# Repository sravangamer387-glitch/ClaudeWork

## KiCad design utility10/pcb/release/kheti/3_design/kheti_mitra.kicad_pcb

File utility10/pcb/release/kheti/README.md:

# Kheti-Mitra irrigation controller - main board (rev B)

Kheti-Mitra irrigation controller: 12 V DC input, 5 V regulator, solenoid-valve driver, two capacitive soil sensors, rain sensor.

**Status: engineering release, software-verified only (ERC on the netlist, KiCad DRC, netlist cross-check, SPICE where noted). Not yet built, not reviewed by a second engineer, not certified.**

## Specification
- Board 86 x 60 mm, 2 layers, 1.6 mm FR-4, 1 oz copper, rounded corners R2.5 mm, 4 x M2.5 mounting holes, 2 fiducials.
- Rules used: min track 0.2 mm (power 0.4 mm), min clearance 0.2 mm, via 0.6/0.3 mm, GND pour on both layers, 132 stitching vias.
- Finish: ENIG recommended (HASL lead-free acceptable); green mask, white silk; IPC class 2.
- 37 parts, 22 nets.

## Circuit description
- 12 V jack -> 1 A PTC -> SMBJ15A TVS -> reverse-polarity PMOS -> +12V; AMS1117-5.0 -> +5V (about 0.3 W at 40 mA).
- Valve: AO3400A low-side switch with 100 ohm gate resistor, 100 k pull-down and SS14 flyback diode; soil sensors on ADC0/ADC1 through 1 k + 100 nF; rain digital input with pull-up.

## Power
Idle about 15 mA at 5 V from 12 V (0.2 W); valve 12 V x 0.3 A during watering.

## Verification
| Check | Result |
|---|---|
| Electrical rule check on the netlist (own ERC: unconnected pins, single-pin nets, output conflicts, unpowered supplies, symbol/footprint pin match) | 0 errors, 0 warnings |
| KiCad DRC | 0 errors, 0 warnings; unconnected pads: 0 |
| Schematic netlist equals PCB netlist | yes |
| Router failures | 0 |
| 3D STEP export | yes |
| Independent Gerber parse (gerbonara): layers parsed, outline size equals the design | 9 layers, outline [86.1, 60.1] mm, match |

Enclosure (prototype shell for 3D printing): outer 101.2 x 75.2 x 23.0 mm, collision/opening check: pass

## Bill of materials
| Ref | Value | Footprint | Manufacturer part | LCSC # | LCSC status |
|---|---|---|---|---|---|
| U1 | ATmega328P-AU | TQFP-32_7x7mm_P0.8mm | ATMEGA328P-AU | C14877 | verified |
| C1 | 100n | C_0603_1608Metric | Samsung CL10B104KB8NNNC 0603 100nF X7R 50V | C1591 | verified |
| C2 | 100n | C_0603_1608Metric | Samsung CL10B104KB8NNNC 0603 100nF X7R 50V | C1591 | verified |
| C3 | 100n | C_0603_1608Metric | Samsung CL10B104KB8NNNC 0603 100nF X7R 50V | C1591 | verified |
| R7 | 10k | R_0603_1608Metric | 0603 10k 1% | C25804 | verified |
| J2 | ISP | PinHeader_2x03_P2.54mm_Vertical | HCTL PZ254-2-03-Z-8.5 (ZHOURI C5116479 had only 340 in stock) | C2894964 | verified |
| D1 | Green | LED_0603_1608Metric | Hubei KENTO KT-0603YG yellow-green 570 nm, Vf about 2 V (lights well from 3.3 V with 1 k; the Everlight 19-217 green was out of stock) | C2289 | verified |
| R5 | 1k | R_0603_1608Metric | 0603 1k 1% | C21190 | verified |
| J1 | 12 V DC in | BarrelJack_CUI_PJ-063AH_Horizontal | CUI/Same Sky PJ-063AH | C22434582 | verified |
| F1 | PTC 1A 16V | Fuse_1812_4532Metric | Littelfuse 1812L110/16DR (1.1 A hold, 16 V) | C142746 | verified |
| D3 | SMBJ15A | D_SMB | Littelfuse SMBJ15A | C83846 | verified |
| Q3 | AO3401A | SOT-23 | AO3401A | C15127 | verified |
| R17 | 100k | R_0603_1608Metric | 0603 100k 1% | C25803 | verified |
| U3 | AMS1117-5.0 | SOT-223-3_TabPin2 | AMS AMS1117-5.0 SOT-223 | C6187 | verified |
| C6 | 10u | C_0805_2012Metric | 0805 10uF X5R | C15850 | verified |
| C7 | 10u | C_0805_2012Metric | 0805 10uF X5R | C15850 | verified |
| C8 | 100n | C_0603_1608Metric | Samsung CL10B104KB8NNNC 0603 100nF X7R 50V | C1591 | verified |
| Q4 | AO3400A | SOT-23 | AOS AO3400A | C20917 | verified |
| R16 | 100 | R_0603_1608Metric | UNI-ROYAL 0603WAF1000T5E | C22775 | verified |
| R18 | 100k | R_0603_1608Metric | 0603 100k 1% | C25803 | verified |
| D7 | SS14 | D_SMA | Starsea SS14 SMA | C84343 | verified |
| J5 | Valve 12V | TerminalBlock_bornier-2_P5.08mm | Cixi Kefa KF128-5.08-2P-AA | C474952 | verified |
| J6 | Soil sensor 1 | JST_PH_B3B-PH-K_1x03_P2.00mm_Vertical | JST B3B-PH-K-S(LF)(SN) | C131339 | verified |
| J7 | Soil sensor 2 | JST_PH_B3B-PH-K_1x03_P2.00mm_Vertical | JST B3B-PH-K-S(LF)(SN) | C131339 | verified |
| J8 | Rain sensor | JST_PH_B3B-PH-K_1x03_P2.00mm_Vertical | JST B3B-PH-K-S(LF)(SN) | C131339 | verified |
| R20 | 1k | R_0603_1608Metric | 0603 1k 1% | C21190 | verified |
| C9 | 100n | C_0603_1608Metric | Samsung CL10B104KB8NNNC 0603 100nF X7R 50V | C1591 | verified |
| R21 | 1k | R_0603_1608Metric | 0603 1k 1% | C21190 | verified |
| C10 | 100n | C_0603_1608Metric | Samsung CL10B104KB8NNNC 0603 100nF X7R 50V | C1591 | verified |
| R22 | 1k | R_0603_1608Metric | 0603 1k 1% | C21190 | verified |
| R23 | 10k | R_0603_1608Metric | 0603 10k 1% | C25804 | verified |
| C11 | 100n | C_0603_1608Metric | Samsung CL10B104KB8NNNC 0603 100nF X7R 50V | C1591 | verified |
| SW2 | Hold | SW_SPST_B3U-1000P | Omron B3U-1000P | C231329 | verified |
| TP1 | TP | TestPoint_Pad_D1.5mm |  |  |  |
| TP2 | TP | TestPoint_Pad_D1.5mm |  |  |  |
| TP3 | TP | TestPoint_Pad_D1.5mm |  |  |  |
| TP4 | TP | TestPoint_Pad_D1.5mm |  |  |  |

`verified` = LCSC number confirmed by web search on 2026-10-31/11-01; `memory` = from my recollection, **check on lcsc.com before ordering**; empty = no number chosen (through-hole connectors, switches, buzzer, test points: hand-assembled or chosen by the buyer). `*_JLC_BOM.csv` / `*_JLC_CPL.csv` list only the parts with an LCSC number; JLCPCB rotation corrections (CPL) must be checked in their viewer.

## Assembly notes
- Reflow (JLCPCB SMT): all SMD parts with an LCSC number. Hand-solder: JST connectors, pin headers, buzzer, switches, test points as listed in the BOM. Fiducials and mounting holes are in the Gerbers.
- Polarity: LED cathode toward GND (silk marks), electrolytic none, diode D2 cathode to +V, Q2 orientation as footprint (SOT-23 pin 1 = gate).
- Programming: ISP header J2 (pin 1 = MISO, square pad). Flash the matching image from `utility10/firmware/release/`: Seeti Counter `4MHz/seeti_prod.hex` (production firmware: timer-triggered 16 kS/s ADC, scan mode to find the real whistle frequency, battery check), Rain Alert `8MHz/rain_alert.hex`, Bijli Meter Reader `8MHz/bijli_meter.hex` (demo-grade firmware, to be hardened).

## Bring-up and test
1. Jack: +12V = 11.9 V, +5V = 5.0 V.
2. Force VALVE_G high from the ISP: the valve switches and the Schottky catches the flyback.
3. Soil sensors: dry about 520 counts / wet about 260 counts (to be calibrated).

## Files
`1_fabrication/` Gerber + drill zip (upload to JLCPCB/any fab), fab notes, copper plot
`2_assembly/` JLC BOM + CPL (SMD parts JLC assembles), full BOM with LCSC numbers for every part, pick-and-place, assembly drawing
`3_design/` KiCad 7 project (pcb, schematic, libs), netlist, STEP model, schematic PDF, renders
`4_enclosure/` printable enclosure (base, screwed lid, battery door, plungers / light pipes / switch extensions) or a mounting plate for a bought IP65 box; dimensions and notes in enclosure.json
`5_verification/` DRC, ERC, verification and readiness reports

## Known limits and review checklist
- Layout was produced by a custom router and software placement; a human layout review (analog routing, ground returns, creepage, connector mechanics, silkscreen) is still required.
- Not verified: EMC, ESD (apart from TVS parts where fitted), thermal, real component tolerances, supplier stock/price, assembly house design-for-manufacture check (run JLCPCB's DFM check on the Gerbers).
- Firmware thresholds are placeholders to be calibrated on prototypes.

## Manufacturing readiness (automatic check)

| Check | Result |
|---|---|
| gerber layers and drill present | PASS |
| drc errors 0 | PASS |
| unconnected 0 | PASS |
| netlist matches schematic | PASS |
| erc errors 0 | PASS |
| independent gerber check clean | PASS |
| every part has lcsc number | PASS |
| every lcsc number verified | PASS |
| cpl rows equal jlc bom parts | PASS |
| step model | PASS |
| KiCad DRC warnings | 0 |
| **Order ready** | **YES** |

Order steps: (1) upload `1_fabrication/*_gerbers.zip`; (2) for assembly upload `2_assembly/*_JLC_BOM.csv` and `*_JLC_CPL.csv`, check the 3D/rotation preview for every polarised part (diodes, ICs, LEDs, electrolytics) because CPL rotations are generated, not hand-checked; (3) buy the through-hole parts listed in `*_BOM_full.csv` marked hand/THT and solder them; (4) re-check stock and the exact LCSC listing for every line before paying.

Limits: the layout is software-generated and has not been reviewed by a PCB engineer; no prototype has been built; the first batch should be treated as a prototype run (order 5 boards).

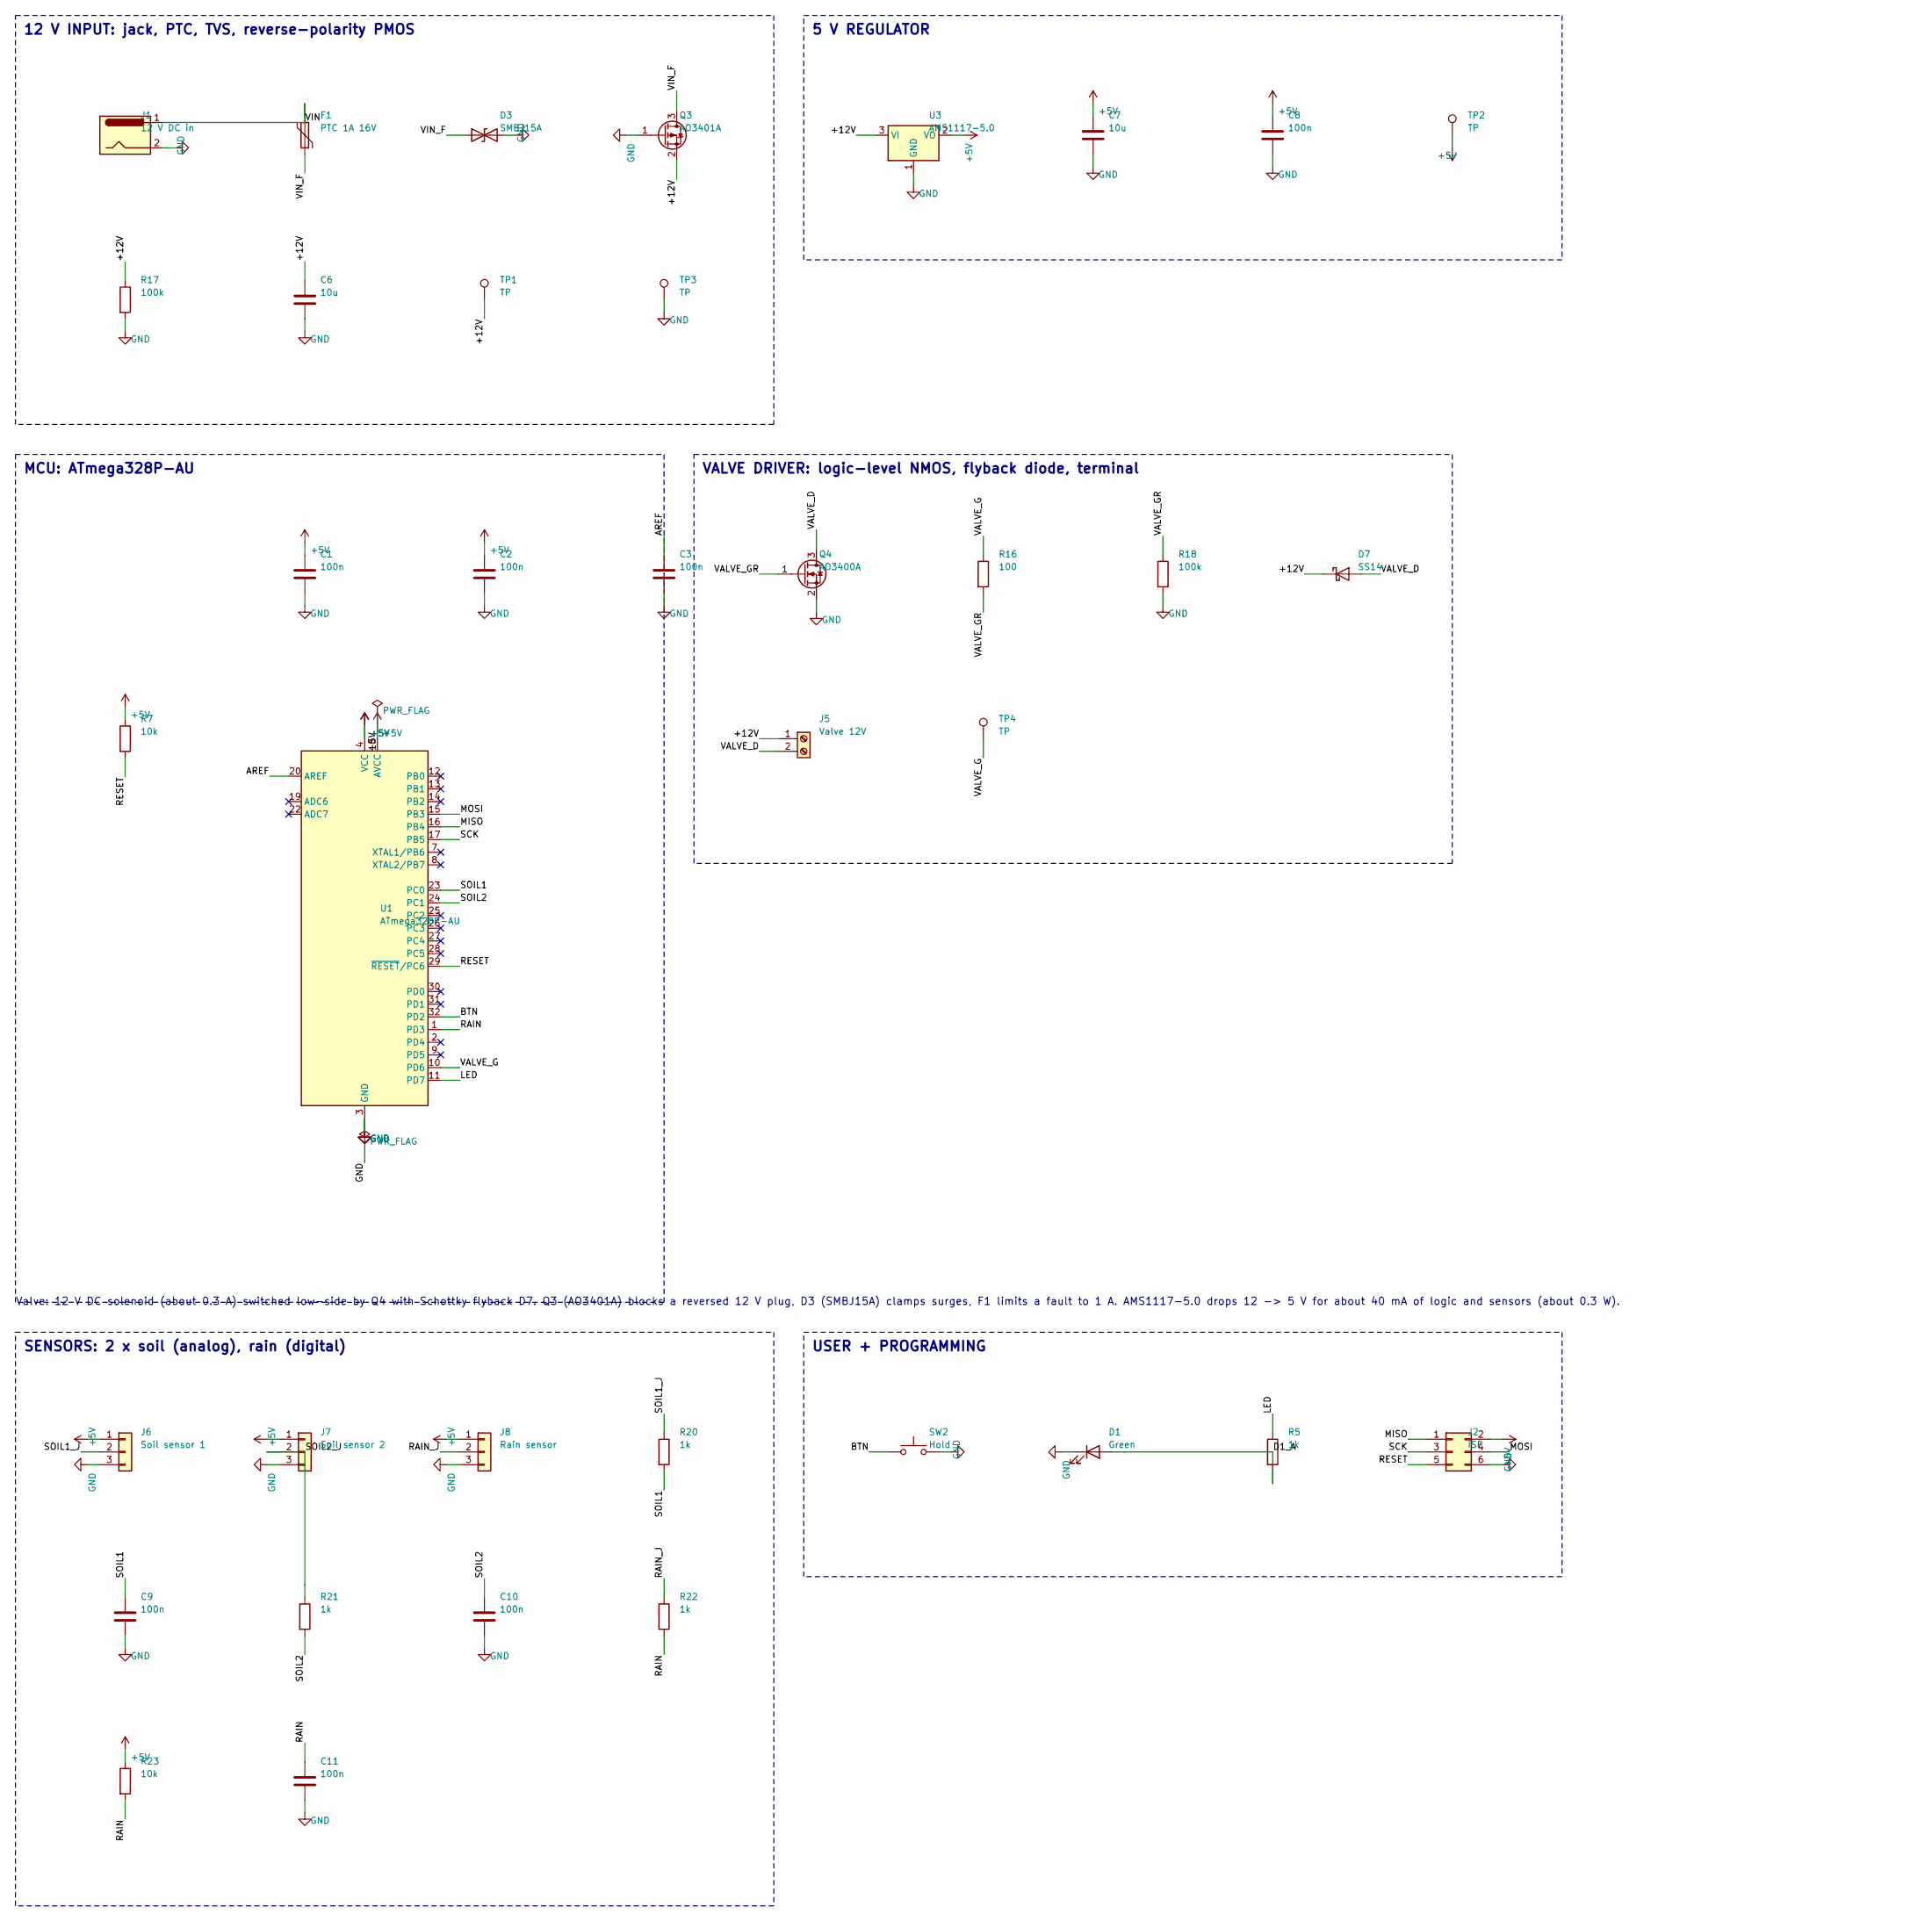
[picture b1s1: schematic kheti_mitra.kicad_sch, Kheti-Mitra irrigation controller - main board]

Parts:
C1, C2, C3, C8, C9, C10, C11: 100n; C_0603_1608Metric
C6, C7: 10u; C_0805_2012Metric
D1: Green; LED_0603_1608Metric
D3: SMBJ15A; D_SMB
D7: SS14; D_SMA
F1: PTC 1A 16V; Fuse_1812_4532Metric
J1: 12 V DC in; BarrelJack_CUI_PJ-063AH_Horizontal
J2: ISP; PinHeader_2x03_P2.54mm_Vertical
J5: Valve 12V; TerminalBlock_bornier-2_P5.08mm
J6: Soil sensor 1; JST_PH_B3B-PH-K_1x03_P2.00mm_Vertical
J7: Soil sensor 2; JST_PH_B3B-PH-K_1x03_P2.00mm_Vertical
J8: Rain sensor; JST_PH_B3B-PH-K_1x03_P2.00mm_Vertical
Q3: AO3401A; SOT-23
Q4: AO3400A; SOT-23
R5, R20, R21, R22: 1k; R_0603_1608Metric
R7, R23: 10k; R_0603_1608Metric
R16: 100; R_0603_1608Metric
R17, R18: 100k; R_0603_1608Metric
SW2: Hold; SW_SPST_B3U-1000P
TP1, TP2, TP3, TP4: TP; TestPoint_Pad_D1.5mm
U1: ATmega328P-AU; TQFP-32_7x7mm_P0.8mm
U3: AMS1117-5.0; SOT-223-3_TabPin2

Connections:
+5V: C1.1, C2.1, C7.1, C8.1, J2.2, J6.1, J7.1, J8.1, R7.1, R23.1, TP2.1, U1.4 (VCC), U1.6 (VCC), U1.18 (AVCC), U3.2 (VO)
+12V: C6.1, D7.1 (K), J5.1, Q3.2 (S), R17.1, TP1.1, U3.3 (VI)
AREF: C3.1, U1.20 (AREF)
BTN: SW2.1, U1.32 (PD2)
D1_A: D1.2 (A), R5.2
GND: C1.2, C2.2, C3.2, C6.2, C7.2, C8.2, C9.2, C10.2, C11.2, D1.1 (K), D3.2 (A2), J1.2, J2.6, J6.3, J7.3, J8.3, Q3.1 (G), Q4.2 (S), R17.2, R18.2, SW2.2, TP3.1, U1.3 (GND), U1.5 (GND), U1.21 (GND), U3.1 (GND)
LED: R5.1, U1.11 (PD7)
MISO: J2.1, U1.16 (PB4)
MOSI: J2.4, U1.15 (PB3)
RAIN: C11.1, R22.2, R23.2, U1.1 (PD3)
RAIN_J: J8.2, R22.1
RESET: J2.5, R7.2, U1.29 (~RESET/PC6)
SCK: J2.3, U1.17 (PB5)
SOIL1: C9.1, R20.2, U1.23 (PC0)
SOIL1_J: J6.2, R20.1
SOIL2: C10.1, R21.2, U1.24 (PC1)
SOIL2_J: J7.2, R21.1
VALVE_D: D7.2 (A), J5.2, Q4.3 (D)
VALVE_G: R16.1, TP4.1, U1.10 (PD6)
VALVE_GR: Q4.1 (G), R16.2, R18.1
VIN: F1.1, J1.1
VIN_F: D3.1 (A1), F1.2, Q3.3 (D)

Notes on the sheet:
12 V INPUT: jack, PTC, TVS, reverse-polarity PMOS
5 V REGULATOR
MCU: ATmega328P-AU
VALVE DRIVER: logic-level NMOS, flyback diode, terminal
SENSORS: 2 x soil (analog), rain (digital)
USER + PROGRAMMING
Valve: 12 V DC solenoid (about 0.3 A) switched low-side by Q4 with Schottky flyback D7. Q3 (AO3401A) blocks a reversed 12 V plug, D3 (SMBJ15A) clamps surges, F1 limits a fault to 1 A. AMS1117-5.0 drops 12 -> 5 V for about 40 mA of logic and sensors (about 0.3 W).

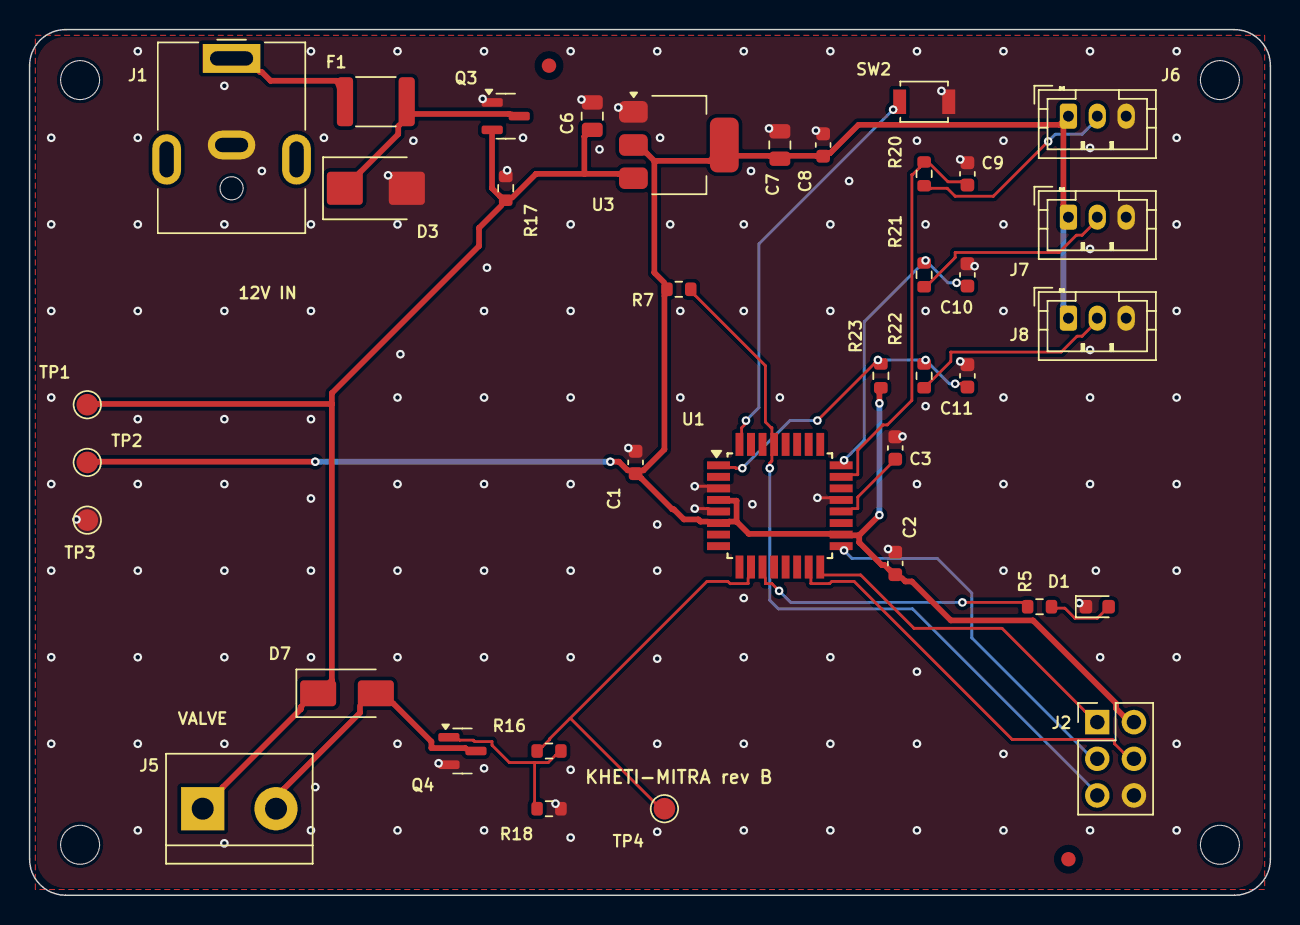
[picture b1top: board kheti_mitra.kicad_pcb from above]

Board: 2 copper layers, 86.0 x 60.0 mm, 43 parts (0 on the bottom side), 22 nets.

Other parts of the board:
FID1, FID2: Fiducial; Fiducial_1mm_Mask2mm
H1, H2, H3, H4: M2.5; MountingHole_2.7mm_M2.5

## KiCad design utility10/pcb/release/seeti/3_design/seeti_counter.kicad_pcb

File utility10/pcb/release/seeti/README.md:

# Seeti Counter - main board (rev B)

Clip-on pressure-cooker whistle counter: electret microphone, band-pass amplifier, ATmega328P-AU, buzzer, LED, 2 x AAA.

**Status: engineering release, software-verified only (ERC on the netlist, KiCad DRC, netlist cross-check, SPICE where noted). Not yet built, not reviewed by a second engineer, not certified.**

## Specification
- Board 64 x 44 mm, 2 layers, 1.6 mm FR-4, 1 oz copper, rounded corners R2.5 mm, 4 x M2.5 mounting holes, 2 fiducials.
- Rules used: min track 0.2 mm (power 0.4 mm), min clearance 0.2 mm, via 0.6/0.3 mm, GND pour on both layers, 54 stitching vias.
- Finish: ENIG recommended (HASL lead-free acceptable); green mask, white silk; IPC class 2.
- 36 parts, 24 nets.

## Circuit description
- **Power:** 2 x AAA (3.0 V fresh, about 2.0 V end of life) -> slide switch SW1 -> AO3401A P-MOSFET Q2 (drain = battery side, source = load, gate = GND) = reverse-battery protection with about 50 mV drop. **Clock:** the ATmega328P is specified for 8 MHz only at 2.7 V and above (1.8 V is allowed up to 4 MHz), and two AAA cells fall below 2.7 V about half-way through their life, so the firmware must switch to 4 MHz at boot (`clock_prescale_set(clock_div_2)`, F_CPU = 4 MHz; ADC clock and the 8 kHz audio sampling still work). Check the speed-grade graph in the current datasheet.
- **Microphone amplifier:** electret capsule biased through R1 2.2 k; AC-coupled (C5 1 uF) into an MCP6001 (rail-to-rail, 1 MHz GBW) non-inverting stage biased at VCC/2 (R2/R3 100 k + C7 10 uF so the feedback return is low impedance). Gain 1 + R8/R9 = 1 + 33k/1k = 34 (SPICE 32.9x at 2.8 kHz); C6 220 nF in the feedback return gives a high-pass at 1/(2 pi R9 C6) = 720 Hz which rejects 100 Hz mains hum and cooking noise before the whistle tone (about 2.8 kHz, to be measured). The amplifier stays flat to about 26 kHz, so **R10 1k + C9 22 nF form a 7.2 kHz first-order anti-alias filter** in front of the ADC; with 16 kS/s sampling this is only a mild filter (about 8 dB at 16 kHz): a known limitation.
- **Digital:** ADC0 reads the amplifier; buzzer through MMBT3904 with flyback diode; button on PD2, LED on PD7; ISP header and a 4-pin UART header (115200 baud debug); reset pulled up by 10 k.

### Simulation: `sim/seeti_amp_results.txt`
```
Closed-loop small-signal response of the Seeti microphone amplifier (Rf = 33k, Rg = 1k, Cg = 220 nF, ideal capsule current source into R1 = 2.2k; MCP6001-class op-amp macro model, GBW 1 MHz) followed by the anti-alias filter R10 1k / C9 22n (-3 dB at 7.2 kHz):
gain at 30 Hz        = 4.4 dB
gain at 1 kHz         = 28.7 dB
gain at 2.8 kHz at amplifier output = 30.4 dB (32.9x); at the ADC pin = 29.7 dB
amplifier -3 dB band  = 700 Hz ... 26.1 kHz (relative to the 30.3 dB passband)
at the ADC pin: 8 kHz = 26.9 dB, 12 kHz = 24.1 dB, 16 kHz = 21.5 dB (relative to 0 dB input)
Production firmware should sample at 16 kS/s (Nyquist 8 kHz): the filter then removes about 8 dB of anything near 16 kHz relative to the 2.8 kHz whistle band. The 8 kS/s demo firmware has little anti-aliasing and relies on the narrow Goertzel bin.
```

### Simulation: `sim/seeti_headroom.txt`
```
Closed-loop gain at 2.8 kHz: 32.8x
VCC 3.0 V: output can swing +/-1.47 V around VMID -> undistorted mic input up to 45 mV peak; a 3 mV peak whistle gives 98 mV peak = 34 ADC counts peak
VCC 2.0 V: output can swing +/-0.97 V around VMID -> undistorted mic input up to 30 mV peak; a 3 mV peak whistle gives 98 mV peak = 50 ADC counts peak
```

## Power
Run current estimate: MCU at 4 MHz and 3 V about 2 mA, amplifier 0.1 mA, microphone bias up to 0.5 mA, LED 1 mA when lit: about 3.6 mA -> 2 x AAA (about 1000 mAh to 2.0 V) gives roughly 250 h of cooking time (estimate, not measured). Add sleep modes in firmware if the unit will stay switched on.

## Verification
| Check | Result |
|---|---|
| Electrical rule check on the netlist (own ERC: unconnected pins, single-pin nets, output conflicts, unpowered supplies, symbol/footprint pin match) | 0 errors, 0 warnings |
| KiCad DRC | 0 errors, 0 warnings; unconnected pads: 0 |
| Schematic netlist equals PCB netlist | yes |
| Router failures | 0 |
| 3D STEP export | yes |
| Independent Gerber parse (gerbonara): layers parsed, outline size equals the design | 9 layers, outline [64.1, 44.1] mm, match |

Enclosure (prototype shell for 3D printing): outer 79.2 x 59.2 x 35.8 mm, collision/opening check: pass

## Bill of materials
| Ref | Value | Footprint | Manufacturer part | LCSC # | LCSC status |
|---|---|---|---|---|---|
| U1 | ATmega328P-AU | TQFP-32_7x7mm_P0.8mm | ATMEGA328P-AU | C14877 | verified |
| U2 | MCP6001 | SOT-23-5 | MCP6001T-I/OT | C116490 | verified |
| J1 | BATT 2xAAA | JST_PH_B2B-PH-K_1x02_P2.00mm_Vertical | JST B2B-PH-K-S(LF)(SN) | C131337 | verified |
| SW1 | Power | SW_SPDT_PCM12 | C&K PCM12SMTR | C221841 | verified |
| Q2 | AO3401A | SOT-23 | AO3401A | C15127 | verified |
| J2 | ISP | PinHeader_2x03_P2.54mm_Vertical | HCTL PZ254-2-03-Z-8.5 (ZHOURI C5116479 had only 340 in stock) | C2894964 | verified |
| J3 | MIC electret | JST_PH_B2B-PH-K_1x02_P2.00mm_Vertical | JST B2B-PH-K-S(LF)(SN) | C131337 | verified |
| J4 | UART | PinHeader_1x04_P2.54mm_Vertical | ZHOURI 2.54-1*4 | C5116483 | verified |
| BZ1 | Buzzer 3V | Buzzer_12x9.5RM7.6 | YUEXIN KC1206 16 ohm passive magnetic 12x9.5 mm (2048 Hz) | C781869 | verified |
| Q1 | MMBT3904 | SOT-23 | MMBT3904 | C20526 | verified |
| D2 | 1N4148WS | D_SOD-323 | 1N4148WS | C2128 | verified |
| SW2 | Target | SW_SPST_B3U-1000P | Omron B3U-1000P | C231329 | verified |
| D1 | Green | LED_0603_1608Metric | Hubei KENTO KT-0603YG yellow-green 570 nm, Vf about 2 V (lights well from 3.3 V with 1 k; the Everlight 19-217 green was out of stock) | C2289 | verified |
| R1 | 2.2k | R_0603_1608Metric | 0603 2.2k 1% | C4190 | verified |
| R2 | 100k | R_0603_1608Metric | 0603 100k 1% | C25803 | verified |
| R3 | 100k | R_0603_1608Metric | 0603 100k 1% | C25803 | verified |
| R4 | 100k | R_0603_1608Metric | 0603 100k 1% | C25803 | verified |
| R5 | 1k | R_0603_1608Metric | 0603 1k 1% | C21190 | verified |
| R6 | 1k | R_0603_1608Metric | 0603 1k 1% | C21190 | verified |
| R7 | 10k | R_0603_1608Metric | 0603 10k 1% | C25804 | verified |
| R8 | 33k | R_0603_1608Metric | UNI-ROYAL 0603WAF3302T5E | C4216 | verified |
| R9 | 1k | R_0603_1608Metric | 0603 1k 1% | C21190 | verified |
| C1 | 100n | C_0603_1608Metric | Samsung CL10B104KB8NNNC 0603 100nF X7R 50V | C1591 | verified |
| C2 | 100n | C_0603_1608Metric | Samsung CL10B104KB8NNNC 0603 100nF X7R 50V | C1591 | verified |
| C3 | 100n | C_0603_1608Metric | Samsung CL10B104KB8NNNC 0603 100nF X7R 50V | C1591 | verified |
| C4 | 10u | C_0805_2012Metric | 0805 10uF X5R | C15850 | verified |
| C5 | 1u | C_0603_1608Metric | 0603 1uF X7R | C15849 | verified |
| C6 | 220n | C_0603_1608Metric | Samsung CL10B224KB8NNNC X7R 50V | C64705 | verified |
| C7 | 10u | C_0805_2012Metric | 0805 10uF X5R | C15850 | verified |
| C8 | 100n | C_0603_1608Metric | Samsung CL10B104KB8NNNC 0603 100nF X7R 50V | C1591 | verified |
| R10 | 1k | R_0603_1608Metric | 0603 1k 1% | C21190 | verified |
| C9 | 22n | C_0603_1608Metric | Samsung CL10B223KB8NNNC X7R | C21122 | verified |
| TP1 | TP | TestPoint_Pad_D1.5mm |  |  |  |
| TP2 | TP | TestPoint_Pad_D1.5mm |  |  |  |
| TP3 | TP | TestPoint_Pad_D1.5mm |  |  |  |
| TP4 | TP | TestPoint_Pad_D1.5mm |  |  |  |

`verified` = LCSC number confirmed by web search on 2026-10-31/11-01; `memory` = from my recollection, **check on lcsc.com before ordering**; empty = no number chosen (through-hole connectors, switches, buzzer, test points: hand-assembled or chosen by the buyer). `*_JLC_BOM.csv` / `*_JLC_CPL.csv` list only the parts with an LCSC number; JLCPCB rotation corrections (CPL) must be checked in their viewer.

## Assembly notes
- Reflow (JLCPCB SMT): all SMD parts with an LCSC number. Hand-solder: JST connectors, pin headers, buzzer, switches, test points as listed in the BOM. Fiducials and mounting holes are in the Gerbers.
- Polarity: LED cathode toward GND (silk marks), electrolytic none, diode D2 cathode to +V, Q2 orientation as footprint (SOT-23 pin 1 = gate).
- Programming: ISP header J2 (pin 1 = MISO, square pad). Flash the matching image from `utility10/firmware/release/`: Seeti Counter `4MHz/seeti_prod.hex` (production firmware: timer-triggered 16 kS/s ADC, scan mode to find the real whistle frequency, battery check), Rain Alert `8MHz/rain_alert.hex`, Bijli Meter Reader `8MHz/bijli_meter.hex` (demo-grade firmware, to be hardened).

## Bring-up and test
1. Insert 2 x AAA with switch OFF; measure BAT_P to GND (J1 pins) = 2.8-3.2 V.
2. Switch ON: TP1 (+3V0) = battery minus about 0.05 V; no heating.
3. VMID (R2/R3 junction) = VCC/2 +-0.05 V; TP3 (MIC_OUT) = VCC/2 +-0.1 V with no sound (same DC at the ADC pin through R10).
4. Flash firmware over ISP (J2): `avrdude -p m328p -c usbasp -U lfuse:w:0xE2:m -U hfuse:w:0xD9:m -U efuse:w:0xFE:m` (internal 8 MHz RC, CKDIV8 off, brown-out 1.8 V; the firmware then divides the clock to 4 MHz).
5. Play a 2.8 kHz tone from a phone at 10 cm: TP3 swings about +-100 mV peak and the firmware counts whistles.

## Files
`1_fabrication/` Gerber + drill zip (upload to JLCPCB/any fab), fab notes, copper plot
`2_assembly/` JLC BOM + CPL (SMD parts JLC assembles), full BOM with LCSC numbers for every part, pick-and-place, assembly drawing
`3_design/` KiCad 7 project (pcb, schematic, libs), netlist, STEP model, schematic PDF, renders
`4_enclosure/` printable enclosure (base, screwed lid, battery door, plungers / light pipes / switch extensions) or a mounting plate for a bought IP65 box; dimensions and notes in enclosure.json
`5_verification/` DRC, ERC, verification and readiness reports

## Known limits and review checklist
- Layout was produced by a custom router and software placement; a human layout review (analog routing, ground returns, creepage, connector mechanics, silkscreen) is still required.
- Not verified: EMC, ESD (apart from TVS parts where fitted), thermal, real component tolerances, supplier stock/price, assembly house design-for-manufacture check (run JLCPCB's DFM check on the Gerbers).
- Firmware thresholds are placeholders to be calibrated on prototypes.

## Manufacturing readiness (automatic check)

| Check | Result |
|---|---|
| gerber layers and drill present | PASS |
| drc errors 0 | PASS |
| unconnected 0 | PASS |
| netlist matches schematic | PASS |
| erc errors 0 | PASS |
| independent gerber check clean | PASS |
| every part has lcsc number | PASS |
| every lcsc number verified | PASS |
| cpl rows equal jlc bom parts | PASS |
| step model | PASS |
| KiCad DRC warnings | 0 |
| **Order ready** | **YES** |

Order steps: (1) upload `1_fabrication/*_gerbers.zip`; (2) for assembly upload `2_assembly/*_JLC_BOM.csv` and `*_JLC_CPL.csv`, check the 3D/rotation preview for every polarised part (diodes, ICs, LEDs, electrolytics) because CPL rotations are generated, not hand-checked; (3) buy the through-hole parts listed in `*_BOM_full.csv` marked hand/THT and solder them; (4) re-check stock and the exact LCSC listing for every line before paying.

Limits: the layout is software-generated and has not been reviewed by a PCB engineer; no prototype has been built; the first batch should be treated as a prototype run (order 5 boards).

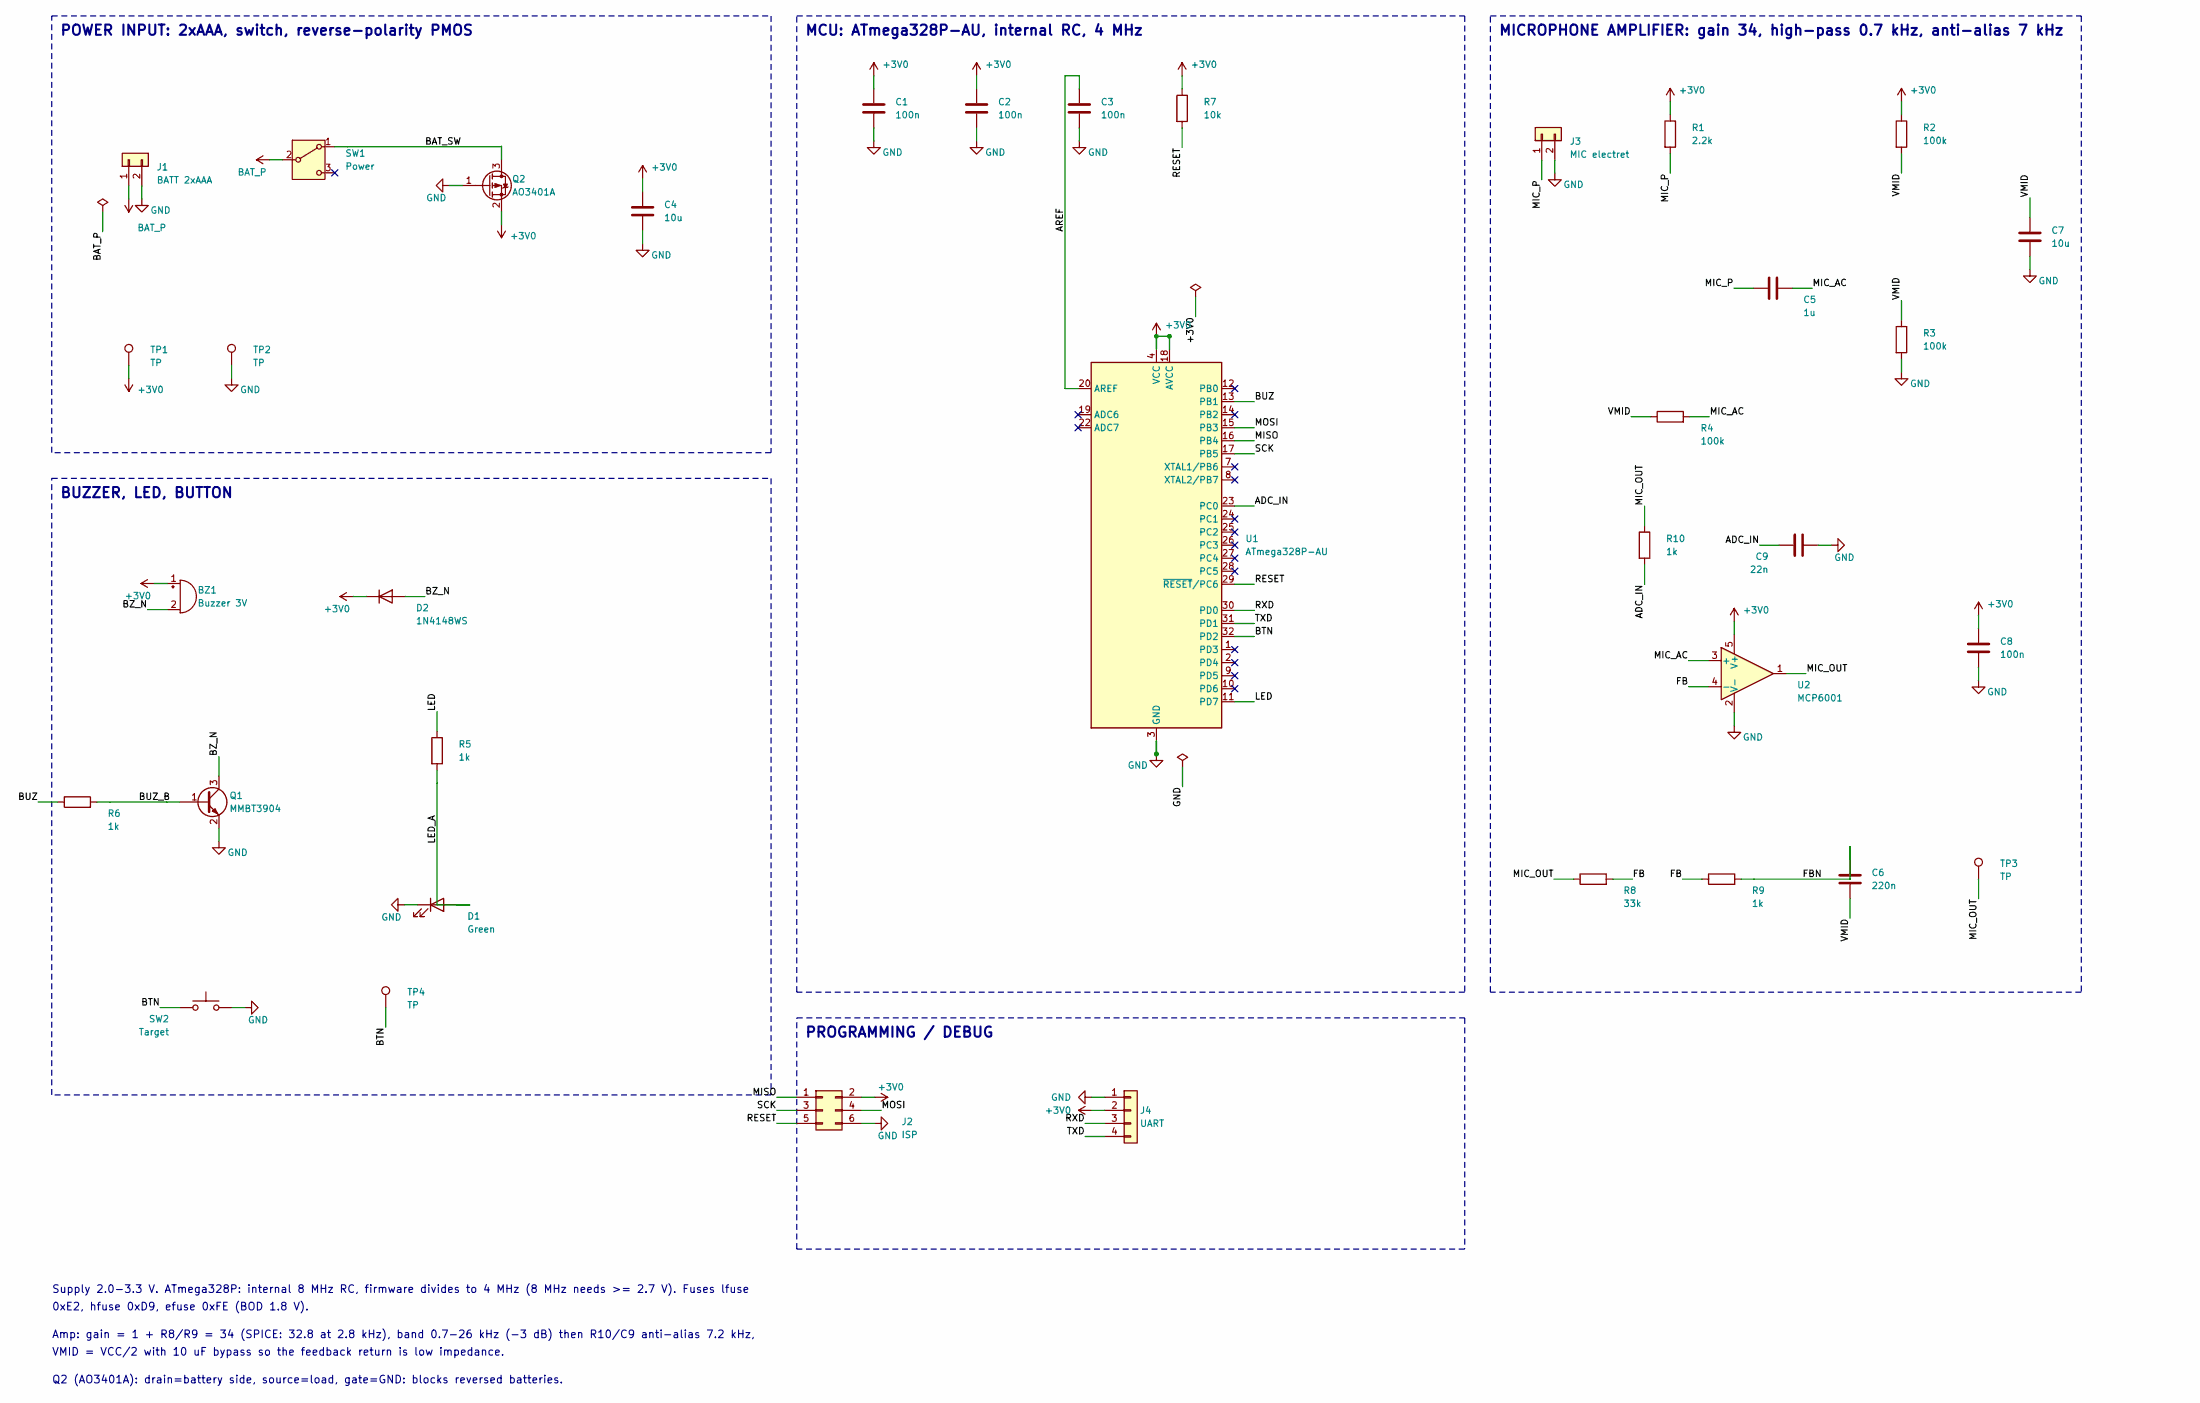
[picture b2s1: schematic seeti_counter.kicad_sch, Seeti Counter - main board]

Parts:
BZ1: Buzzer 3V; Buzzer_12x9.5RM7.6
C1, C2, C3, C8: 100n; C_0603_1608Metric
C4, C7: 10u; C_0805_2012Metric
C5: 1u; C_0603_1608Metric
C6: 220n; C_0603_1608Metric
C9: 22n; C_0603_1608Metric
D1: Green; LED_0603_1608Metric
D2: 1N4148WS; D_SOD-323
J1: BATT 2xAAA; JST_PH_B2B-PH-K_1x02_P2.00mm_Vertical
J2: ISP; PinHeader_2x03_P2.54mm_Vertical
J3: MIC electret; JST_PH_B2B-PH-K_1x02_P2.00mm_Vertical
J4: UART; PinHeader_1x04_P2.54mm_Vertical
Q1: MMBT3904; SOT-23
Q2: AO3401A; SOT-23
R1: 2.2k; R_0603_1608Metric
R2, R3, R4: 100k; R_0603_1608Metric
R5, R6, R9, R10: 1k; R_0603_1608Metric
R7: 10k; R_0603_1608Metric
R8: 33k; R_0603_1608Metric
SW1: Power; SW_SPDT_PCM12
SW2: Target; SW_SPST_B3U-1000P
TP1, TP2, TP3, TP4: TP; TestPoint_Pad_D1.5mm
U1: ATmega328P-AU; TQFP-32_7x7mm_P0.8mm
U2: MCP6001; SOT-23-5

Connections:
+3V0: BZ1.1 (+), C1.1, C2.1, C4.1, C8.1, D2.1 (K), J2.2, J4.2, Q2.2 (S), R1.1, R2.1, R7.1, TP1.1, U1.4 (VCC), U1.6 (VCC), U1.18 (AVCC), U2.5 (V+)
ADC_IN: C9.1, R10.2, U1.23 (PC0)
AREF: C3.1, U1.20 (AREF)
BAT_P: J1.1, SW1.2 (B)
BAT_SW: Q2.3 (D), SW1.1 (A)
BTN: SW2.1, TP4.1, U1.32 (PD2)
BUZ: R6.1, U1.13 (PB1)
BUZ_B: Q1.1 (B), R6.2
BZ_N: BZ1.2 (-), D2.2 (A), Q1.3 (C)
FB: R8.2, R9.1, U2.4 (-)
FBN: C6.1, R9.2
GND: C1.2, C2.2, C3.2, C4.2, C7.2, C8.2, C9.2, D1.1 (K), J1.2, J2.6, J3.2, J4.1, Q1.2 (E), Q2.1 (G), R3.2, SW2.2, TP2.1, U1.3 (GND), U1.5 (GND), U1.21 (GND), U2.2 (V-)
LED: R5.1, U1.11 (PD7)
LED_A: D1.2 (A), R5.2
MIC_AC: C5.2, R4.2, U2.3 (+)
MIC_OUT: R8.1, R10.1, TP3.1, U2.1
MIC_P: C5.1, J3.1, R1.2
MISO: J2.1, U1.16 (PB4)
MOSI: J2.4, U1.15 (PB3)
RESET: J2.5, R7.2, U1.29 (~RESET/PC6)
RXD: J4.3, U1.30 (PD0)
SCK: J2.3, U1.17 (PB5)
TXD: J4.4, U1.31 (PD1)
VMID: C6.2, C7.1, R2.2, R3.1, R4.1

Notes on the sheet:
POWER INPUT: 2xAAA, switch, reverse-polarity PMOS
MCU: ATmega328P-AU, internal RC, 4 MHz
BUZZER, LED, BUTTON
PROGRAMMING / DEBUG
MICROPHONE AMPLIFIER: gain 34, high-pass 0.7 kHz, anti-alias 7 kHz
Supply 2.0-3.3 V. ATmega328P: internal 8 MHz RC, firmware divides to 4 MHz (8 MHz needs >= 2.7 V). Fuses lfuse
0xE2, hfuse 0xD9, efuse 0xFE (BOD 1.8 V).
Amp: gain = 1 + R8/R9 = 34 (SPICE: 32.8 at 2.8 kHz), band 0.7-26 kHz (-3 dB) then R10/C9 anti-alias 7.2 kHz,
VMID = VCC/2 with 10 uF bypass so the feedback return is low impedance.
Q2 (AO3401A): drain=battery side, source=load, gate=GND: blocks reversed batteries.

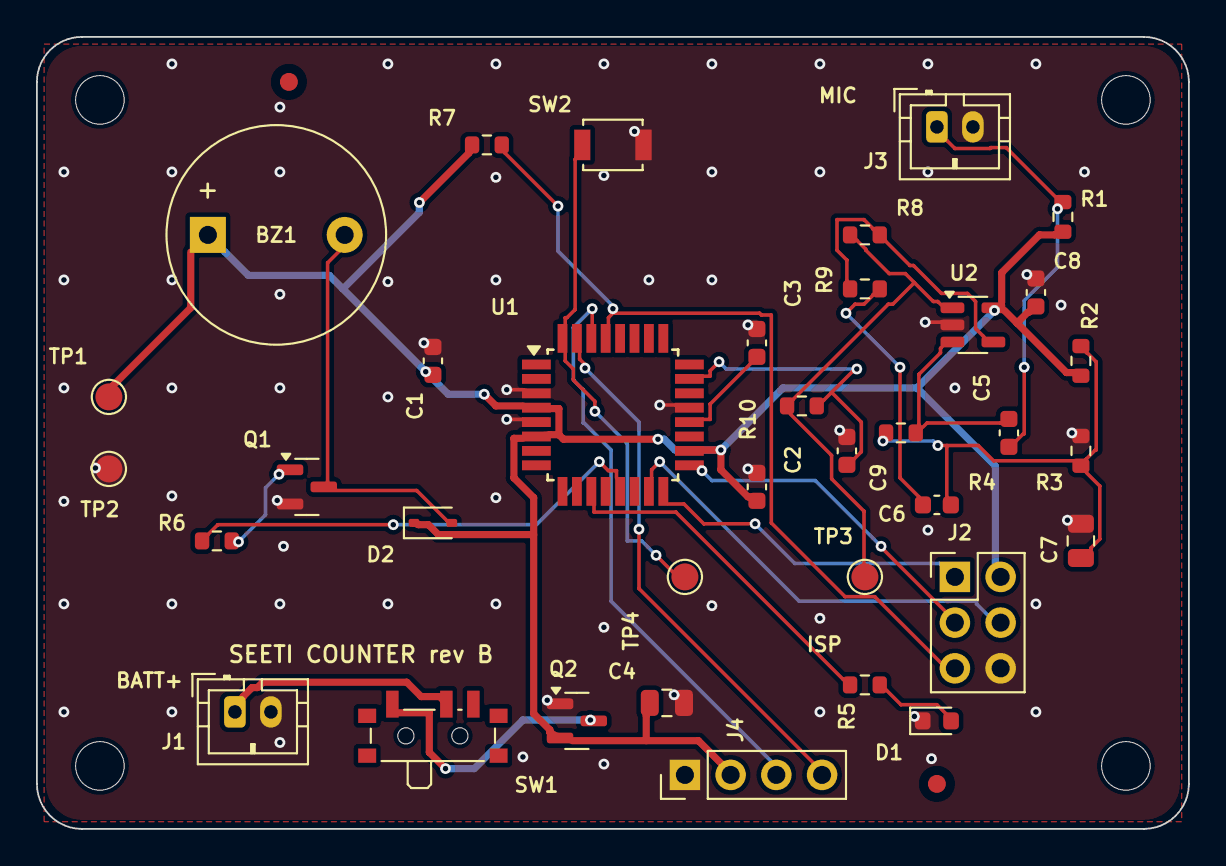
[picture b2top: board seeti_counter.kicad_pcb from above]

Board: 2 copper layers, 64.0 x 44.0 mm, 42 parts (0 on the bottom side), 24 nets.

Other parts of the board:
FID1, FID2: Fiducial; Fiducial_1mm_Mask2mm
H1, H2, H3, H4: M2.5; MountingHole_2.7mm_M2.5
